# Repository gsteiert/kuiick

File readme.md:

# KUIICK Board

## K32L2B USB to IIC Kit

This board is a tiny USB to Qwiic development board in a bread-board friendly DIP form factor.  In addition to micro USB and Qwiic connectors, it also has two buttons, SPI flash and two rows of 100mil pitch header footprints for additional expansion.  The MCU is an NXP K32L2B Arm Cortex-M0+ with crystal-less USB and integrated VBUS to 3V regulator.  All of this is packed into a 15mm X 20mm board.

[Schematic](kuiick_sch.pdf)

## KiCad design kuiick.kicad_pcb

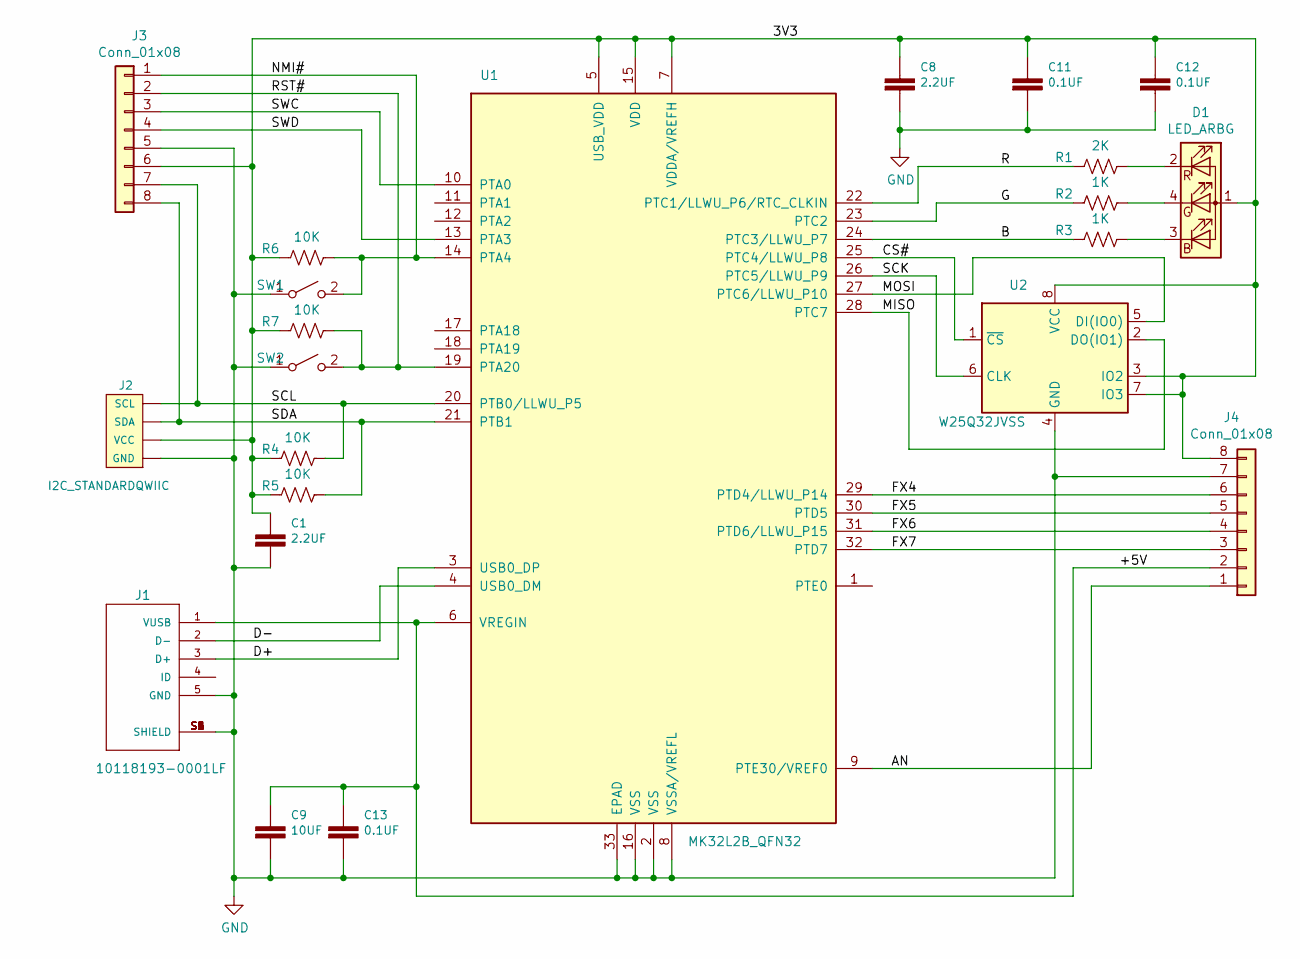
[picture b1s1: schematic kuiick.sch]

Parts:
C1, C8: 2.2UF; C0603
C9: 10UF; C0603
C11, C12, C13: 0.1UF; C0402
D1: LED_ARBG; LED_RGB_1x1mm_CW
J1: 10118193-0001LF; FCI_10118193-0001LF
J2: I2C_STANDARDQWIIC; 1X04_1MM_RA
J3, J4: Conn_01x08; PinHeader_1x08_P100mil_Vertical
R1: 2K; C0402
R2, R3: 1K; C0402
R4, R5, R6, R7: 10K; C0402
SW1, SW2: SW_SPST; SW_SPST_B3U-1000P_tight
U1: MK32L2B_QFN32; QFN-32-1EP_5x5mm_P0.5mm_EP3.45x3.45mm
U2: W25Q32JVSS; SOIC-8_5.23x5.23mm_P1.27mm

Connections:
/3V3: C1.1, C8.1, C11.1, C12.1, D1.1 (A), J2.2 (VCC), J3.6, J4.8, R4.2, R5.2, R6.2, R7.2, U1.5 (USB_VDD), U1.7 (VDDA/VREFH), U1.15 (VDD), U2.3 (IO2), U2.7 (IO3), U2.8 (VCC)
/+5V: C9.1, C13.1, J1.1 (VUSB), J4.2, U1.6 (VREGIN)
/AN: J4.1, U1.9 (PTE30/VREF0)
/B: R3.2, U1.24 (PTC3/LLWU_P7)
/CS#: U1.25 (PTC4/LLWU_P8), U2.1 (~CS)
/D+: J1.3 (D+), U1.3 (USB0_DP)
/D-: J1.2 (D-), U1.4 (USB0_DM)
/FX4: J4.6, U1.29 (PTD4/LLWU_P14)
/FX5: J4.5, U1.30 (PTD5)
/FX6: J4.4, U1.31 (PTD6/LLWU_P15)
/FX7: J4.3, U1.32 (PTD7)
/G: R2.2, U1.23 (PTC2)
/MISO: U1.28 (PTC7), U2.2 (DO(IO1))
/MOSI: U1.27 (PTC6/LLWU_P10), U2.5 (DI(IO0))
/NMI#: J3.1, R6.1, SW1.2 (B), U1.14 (PTA4)
/R: R1.2, U1.22 (PTC1/LLWU_P6/RTC_CLKIN)
/RST#: J3.2, R7.1, SW2.2 (B), U1.19 (PTA20)
/SCK: U1.26 (PTC5/LLWU_P9), U2.6 (CLK)
/SCL: J2.4 (SCL), J3.7, R4.1, U1.20 (PTB0/LLWU_P5)
/SDA: J2.3 (SDA), J3.8, R5.1, U1.21 (PTB1)
/SWC: J3.3, U1.10 (PTA0)
/SWD: J3.4, U1.13 (PTA3)
GND: C1.2, C8.2, C9.2, C11.2, C12.2, C13.2, J1.5 (GND), J1.None, J1.S1 (SHIELD), J1.S2 (SHIELD), J1.S3 (SHIELD), J1.S4 (SHIELD), J1.S5 (SHIELD), J1.S6 (SHIELD), J2.1 (GND), J3.5, J4.7, SW1.1 (A), SW2.1 (A), U1.2 (VSS), U1.8 (VSSA/VREFL), U1.16 (VSS), U1.33 (EPAD), U2.4 (GND)
unnamed: D1.2 (RK), R1.1
unnamed: D1.3 (BK), R3.1
unnamed: D1.4 (GK), R2.1

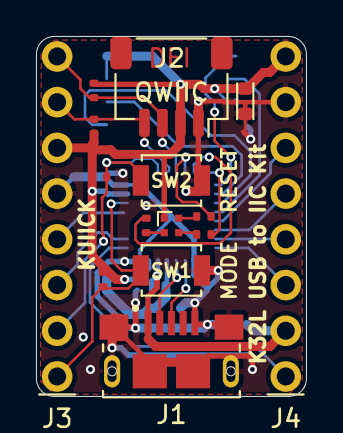
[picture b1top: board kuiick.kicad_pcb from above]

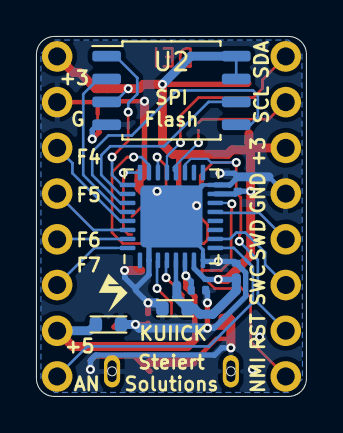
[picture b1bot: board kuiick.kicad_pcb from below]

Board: 2 copper layers, 15.0 x 20.0 mm, 22 parts (7 on the bottom side), 26 nets.

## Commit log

2020-03-21 initial commit, fully routed 14 pin dip
2020-03-22 fully routed dip 16
2020-03-22 cleaned up silk, added logo
2020-03-22 clean up silk, swapped qwiic footprint
2020-03-22 clean up fills
2020-04-04 added schematic in pdf
2020-04-05 added pdf schematic and xyrs file
2020-04-18 added readme and images
2020-04-18 added readme content
2020-05-07 added first power on pic
